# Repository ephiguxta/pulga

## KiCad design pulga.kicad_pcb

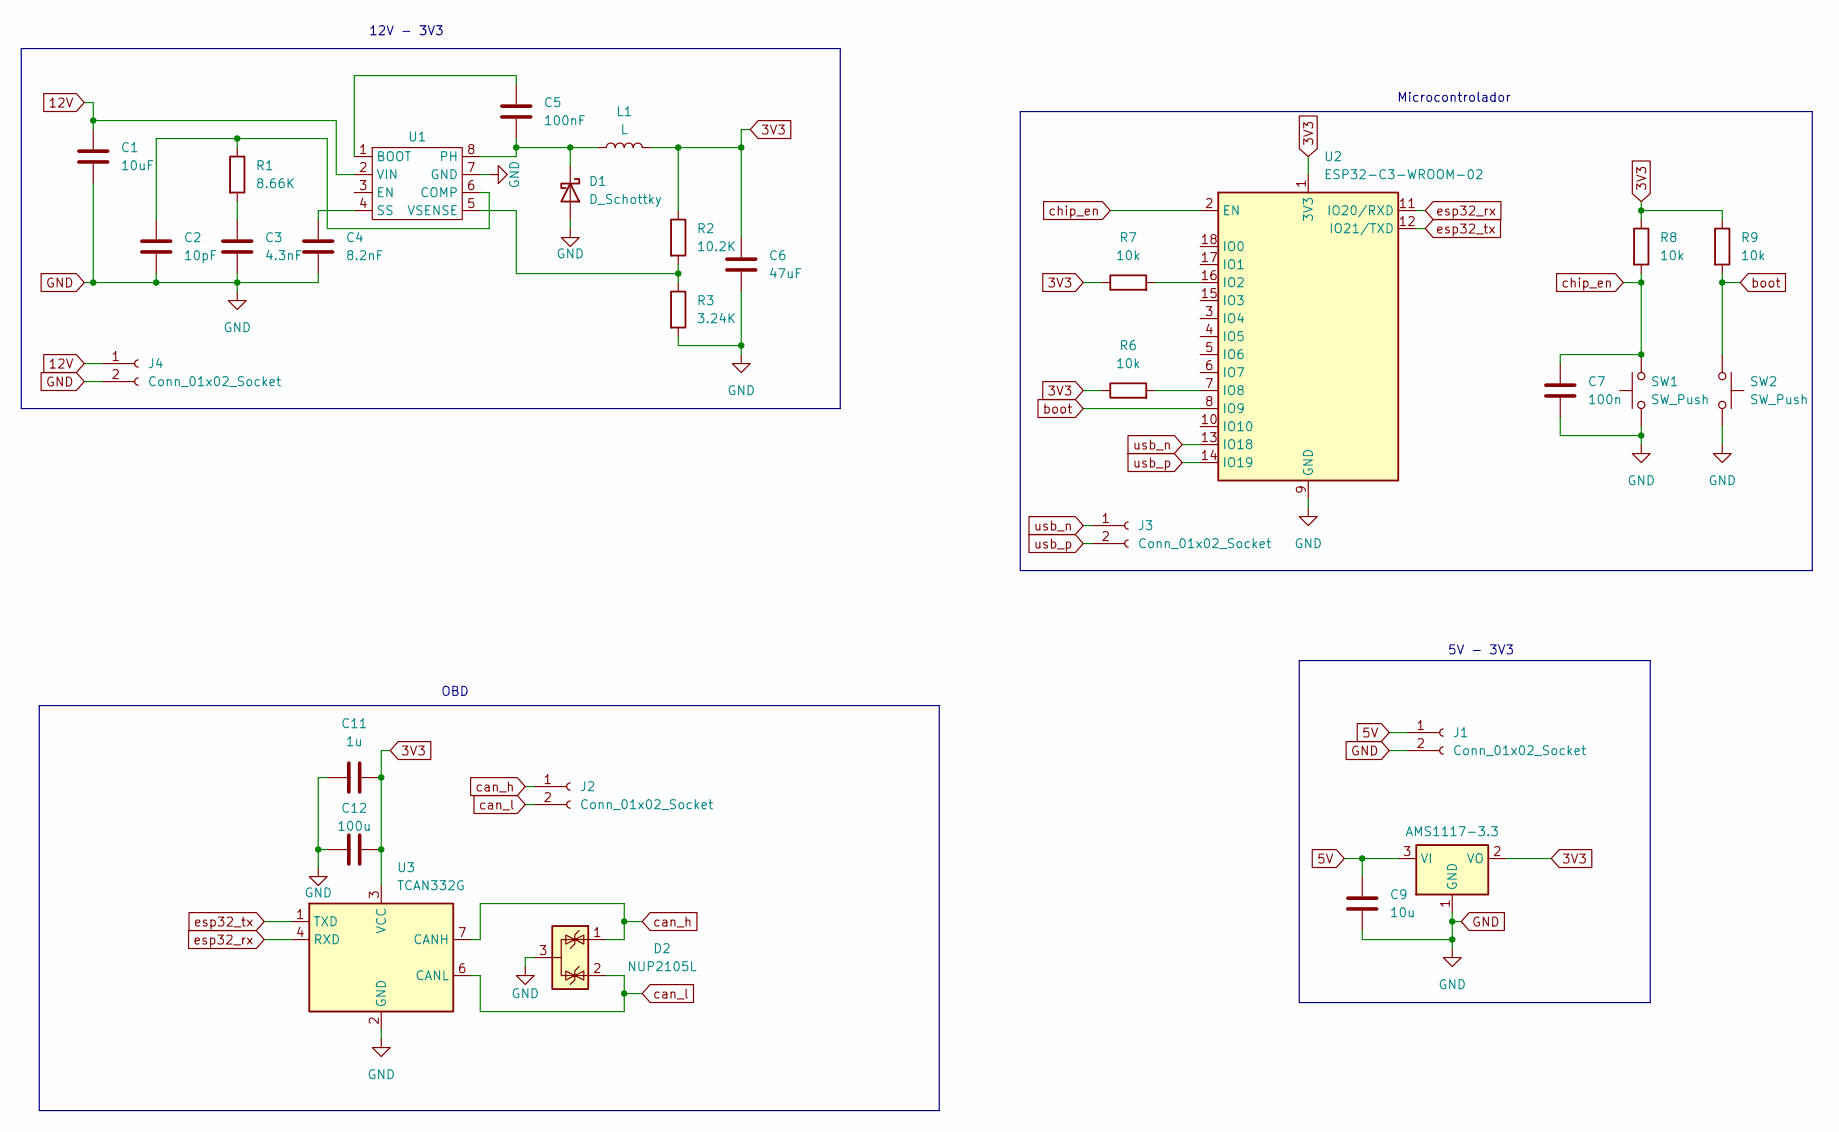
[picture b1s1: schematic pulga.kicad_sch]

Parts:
C1: 10uF; C_1210_3225Metric; LCSC C39232
C2: 10pF; C_0805_2012Metric; LCSC C107107
C3: 4.3nF; C_0201_0603Metric; LCSC C3885982
C4: 8.2nF; C_0201_0603Metric; LCSC C2168104
C5: 100nF; C_0805_2012Metric; LCSC C86041
C6: 47uF; C_1210_3225Metric; LCSC C77101
C7: 100n; C_0201_0603Metric
C9: 10u; C_1206_3216Metric
C11: 1u; C_0201_0603Metric
C12: 100u; C_0201_0603Metric
D1: D_Schottky; D_SMA; LCSC C47460
D2: NUP2105L; SOT-23
J1, J2, J3, J4: Conn_01x02_Socket; two_th_pins
L1: L; L_Cenker_CKCS6045; LCSC C3224592
R1: 8.66K; R_0402_1005Metric; LCSC C185387
R2: 10.2K; R_0402_1005Metric; LCSC C11660
R3: 3.24K; R_0402_1005Metric; LCSC C22369275
R6, R7, R8, R9: 10k; R_0201_0603Metric; LCSC C102690
SW1, SW2: SW_Push; SW_SPST_B3U-1000P; LCSC C231329
U1: SOIC-8_3.9x4.9mm_P1.27mm; LCSC C9865
U2: ESP32-C3-WROOM-02
U3: TCAN332G; SOT-23-8; LCSC C544741
U4: AMS1117-3.3; SOT-223-3_TabPin2

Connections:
3V3: C6.1, C11.2, C12.2, L1.2, R2.1, R6.1, R7.1, R8.1, R9.1, U2.1 (3V3), U3.3 (VCC), U4.2 (VO)
5V: C9.1, J1.1, U4.3 (VI)
12V: C1.1, J4.1, U1.2 (VIN)
GND: C1.2, C2.2, C3.2, C4.2, C6.2, C7.2, C9.2, C11.1, C12.1, D1.2 (A), D2.3 (A), J1.2, J4.2, R3.2, SW1.1, SW2.2, U1.7 (GND), U2.9 (GND), U2.19 (GND), U3.2 (GND), U4.1 (GND); also elsewhere on the board
unnamed: C3.1, R1.2
unnamed: C5.2, D1.1 (K), L1.1, U1.8 (PH)
unnamed: C5.1, U1.1 (BOOT)
unnamed: C2.1, R1.1, U1.6 (COMP)
unnamed: C4.1, U1.4 (SS)
unnamed: R2.2, R3.1, U1.5 (VSENSE)
unnamed: R7.2, U2.16 (IO2)
unnamed: R6.2, U2.7 (IO8)
boot: R9.2, SW2.1, U2.8 (IO9); also elsewhere on the board
can_h: D2.1 (K), J2.1, U3.7 (CANH)
can_l: D2.2 (K), J2.2, U3.6 (CANL)
chip_en: C7.1, R8.2, SW1.2, U2.2 (EN); also elsewhere on the board
esp32_rx: U2.11 (IO20/RXD), U3.4 (RXD)
esp32_tx: U2.12 (IO21/TXD), U3.1 (TXD)
usb_n: J3.1, U2.13 (IO18)
usb_p: J3.2, U2.14 (IO19)

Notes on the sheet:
12V - 3V3
Microcontrolador
OBD
5V - 3V3

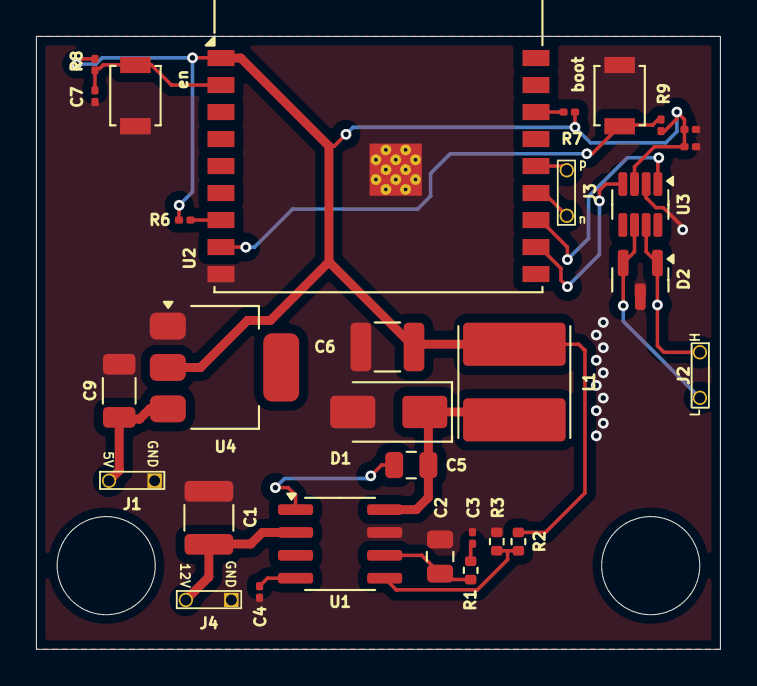
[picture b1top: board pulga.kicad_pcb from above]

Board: 2 copper layers, 38.0 x 34.0 mm, 30 parts (0 on the bottom side), 20 nets.

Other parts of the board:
boot: SW_Push; SW_SPST_B3U-1000P
en: SW_Push; SW_SPST_B3U-1000P

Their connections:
GND: boot.2, en.1; also elsewhere on the board
boot: boot.1; also elsewhere on the board
chip_en: en.2; also elsewhere on the board

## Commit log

2025-10-08 ignorando mais arquivos
2025-10-08 esquemático do conversor buck (~12V pra 3.3V)
2025-10-08 adicionando valor e footprint aos componentes do buck
2025-10-08 correções no esquemático e ligação dos componentes do 54331 na pcb
2025-10-08 aumentando o caminho do GND para parte de cima do circuito
2025-10-08 primeiro commit
2025-10-09 criado os cortes/furas da pcb e limitando o tamanho da pcb para 38x38mm
2025-10-09 inserindo o esp32-c3 e reposicionando o circuito
2025-10-17 adicionando o circuito do transceptor CAN (TCAN332GCDNR) no esquemático
2025-10-17 ligando o circuito do CAN na PCB e corrigindo o esquemático
2025-10-18 ignorando arquivo *bak corretamente
2025-10-18 adicionando sistema de controle para o modo de boot do esp32
2025-10-19 adicionando o esquemático e footprint dos 4 pinos principais (12v, gnd, can_h e can_l) que vem do OBD
2025-10-19 ajeitando os pinos de conexão do OBD
2025-10-19 adicionando as conexões 5v, GND, USB_(P|N) e o LDO
2025-10-20 ignorando os arquivos com outro regex
2025-10-20 adicionando o prl e sch
2025-10-20 centralizando o módulo na folha de PCB e dando nomes as partes no SCH
2025-10-20 adicionando o LCSC aos resistores
2025-10-21 adicionando o LCSC aos componentes do circuito de alimentação 12V-3.3V
2025-10-21 corrigindo a posição de C7 para ficar em paralelo em relação a SW1
2025-10-21 adicionando o LCSC dos botões de bootstrap do esp32
2025-10-22 adicionei o LCSC no TCAN332x
2025-10-22 corrigindo o LCSC do TPS54331
2025-10-23 invertendo a posição do circuito can e ldo; trocando 2 conectores de 4 vias por 4 de 2 vias
2025-10-23 mudando a posição da via de R6
2025-10-23 trocando o pino de 3V3 do AMS1117 para o 2 e não o "dissipador"
2025-10-27 diminuindo o tamanho do texto de referência para todos os componentes
2025-10-27 afastando os pinos do CAN L e H do indutor L1
